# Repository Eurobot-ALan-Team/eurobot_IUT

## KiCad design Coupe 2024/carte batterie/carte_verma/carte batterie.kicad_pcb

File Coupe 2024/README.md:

# eurobot_IUT
docs eurobot_IUT_GEII

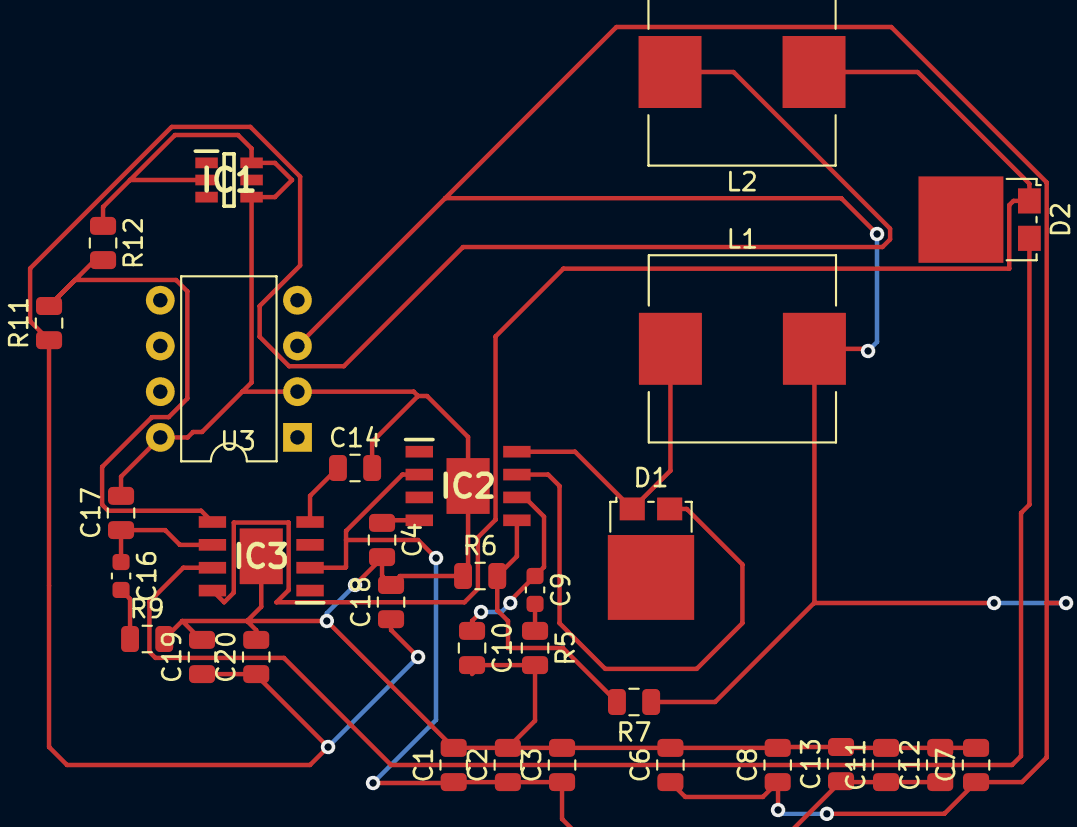
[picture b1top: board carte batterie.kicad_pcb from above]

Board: 2 copper layers, 32 parts (0 on the bottom side), 16 nets.

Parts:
C1, C2, C3, C11, C12, C13: 4.7uf 50V; C_0805_2012Metric
C4, C14: 10nf 200V; C_0805_2012Metric
C6, C7, C8, C18, C19, C20: 22uF 16V; C_0805_2012Metric
C9, C16: 2.2nF 50V; C_0603_1608Metric
C10, C17: 22pF 50V; C_0805_2012Metric
D1, D2: 8A 100V; TO-277A
IC1: TPS3711DDCT; SOT95P280X110-6N
IC2, IC3: TPS54531DDA; SOIC127P600X170-9N
L1, L2: 4.7uH 10.4A; L_Wuerth_HCI-1040
R5, R9: 39K 0.125W; C_0805_2012Metric
R6, R12: 1.96K 0.125W; C_0805_2012Metric
R7, R11: 10.2K 0.125W; C_0805_2012Metric
U3: MCP2551-I-P; DIP-8_W7.62mm

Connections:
+5V: C6.1, C7.1, C8.1, L1.2, R7.1, U3.3 (VDD)
+5Vn2: C18.1, C19.1, C20.1, L2.2, R11.1
+12VS: C1.1, C2.1, C3.1, C11.1, C12.1, C13.1, IC2.2 (VIN), IC3.2 (VIN)
GND: C1.2, C2.2, C3.2, C4.2, C6.2, C7.2, C8.2, C10.2, C11.2, C12.2, C13.2, C14.2, C17.2, C18.2, C19.2, C20.2, IC1.2 (GND_1), IC1.4 (GND_2), IC1.6 (GND_3), IC2.9 (GND_2), IC3.9 (GND_2), R5.2, R6.1, R9.2, R12.1, U3.2 (VSS), U3.8 (Rs)
unnamed: C9.2, R5.1
unnamed: C16.2, R9.1
unnamed: D1.2 (A), IC2.7 (GND_1)
unnamed: D1.1 (K), IC2.8 (PH), L1.1
unnamed: D2.2 (A), IC3.7 (GND_1)
unnamed: D2.1 (K), IC3.8 (PH), L2.1
unnamed: C9.1, C10.1, IC2.6 (COMP)
unnamed: C4.1, IC2.4 (SS)
unnamed: IC2.5 (VSENSE), R6.2, R7.2
unnamed: C16.1, C17.1, IC3.6 (COMP)
unnamed: C14.1, IC3.4 (SS)
unnamed: IC3.5 (VSENSE), R11.2, R12.2

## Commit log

2023-10-11 carte batterie plan
2023-10-11 carte batterie1
2023-10-12 update commande
2023-10-12 ajout doc pour alim a découpage 5V 5A
2023-10-25 Library loader
    ajout des repertoire de library loader
2023-10-25 new compo
2023-10-26 ajout ref carte batterie
2023-10-27 model 3D
2023-12-20 20-12-2023
2023-12-20 rp2040 zero
2024-03-07 modif
2024-03-15 carte bat
2024-03-21 cart bat modif
2024-03-22 docBusCANv1
2024-03-25 pcb cart bat start
2024-04-16 Add files via upload
    Ajout toutes les cartes déjà fait
2024-10-29 Rangement
2024-10-29 sch carte hub
2024-10-29 pcb carte hub
2024-10-29 excel
2024-12-02 modif carte hub fini
2025-02-18 aruco
2025-02-25 Create test_vide
2025-02-25 pied
2025-02-25 Create CodeMoteurs2024
2025-02-25 Create IMPORTANT!!!!!
2025-03-11 code esp32
    code esp32 et rm of tache
2025-04-21 add carte bat
2025-04-29 fg
    #include "mbed.h"
    DigitalOut r5(PB_1),r12(PF_0),r15(PF_1);
    AnalogIn bat1(PA_4),bat2(PA_3),mesure5(PA_5),mesure12(PA_6),mesure15(PA_7);
    int main() {
    while(1) {
    printf("tension batterie 1 : %.2lf V\n\r",14.65*bat1.read());
2025-05-12 Create nrf code main.cpp
    code nrf avec deux fonction de sync utiliser la biblio nrf
2025-05-14 addresse can
2025-05-21 UpdateCarteBatt
    Mise à jour version carte Batterie
2025-05-21 ajout PDF
2025-05-22 Fichiers de Vinzen
    Fichiers pour gérer la communication nrf entre raspberry et mbed.
2025-05-26 Mise à jour Répertoire Groupie
2025-05-29 Prog Homologation PAMI
2025-05-29 ajout .BIN
